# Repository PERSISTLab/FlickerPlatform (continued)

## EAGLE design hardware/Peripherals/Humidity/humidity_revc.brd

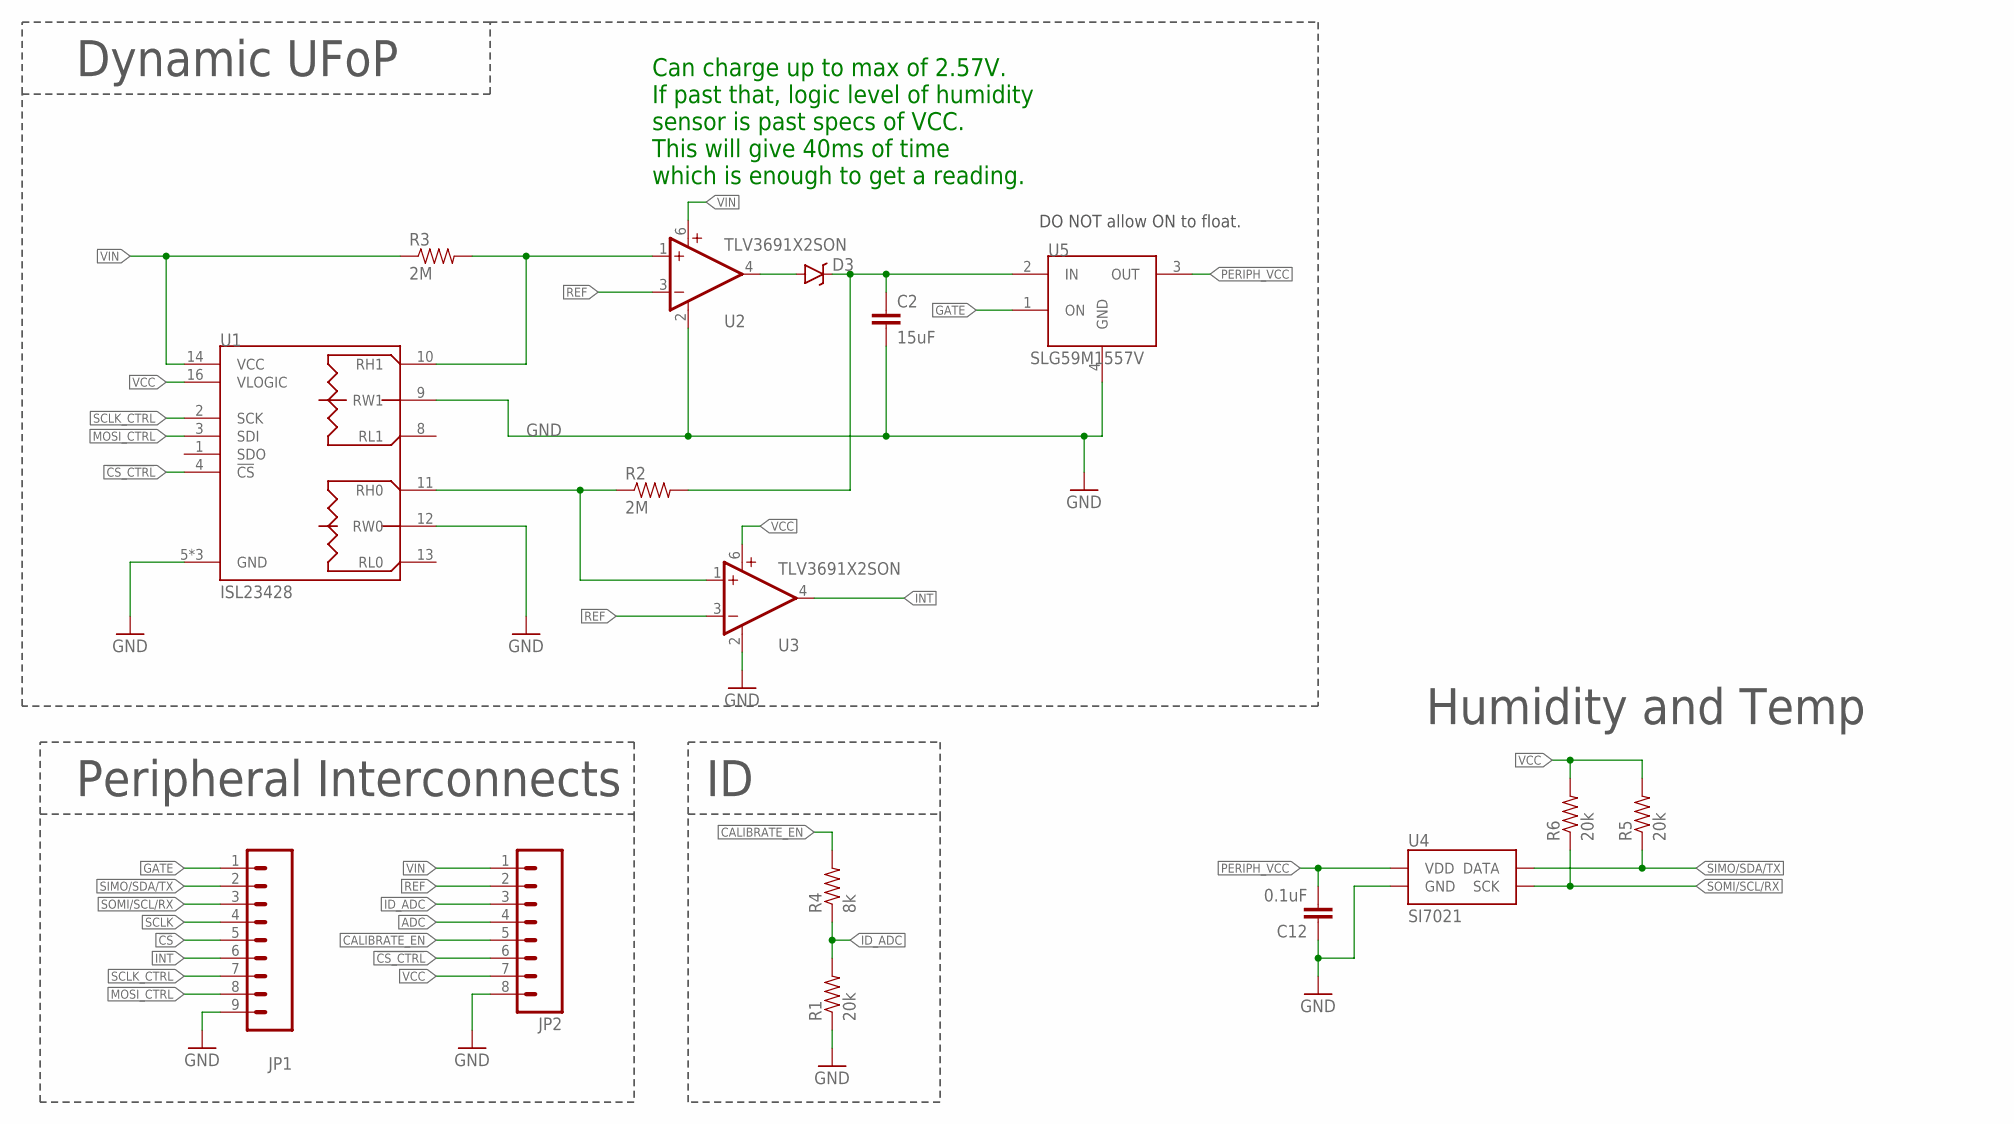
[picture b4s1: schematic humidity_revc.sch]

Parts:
C2: 15uF; 0805; MPN C2012X7S1A156M125AC; DIGIKEY 445-14559-1-ND
C12: 0.1uF; 0402; MPN 0402YD104KAT2A
D3: RB751; SOD-523; MPN BAS40-02V-V-G-08; DIGIKEY BAS40-02V-V-G-08GICT-ND
JP1: M091.27MM; 1X09-1.27MM; MANUFACTURERPARTNUMBER GRPB091VWVN-RC; DIGIKEY S9014E-09-ND
JP2: M081.27MM; 1X08-1.27MM; MANUFACTURERPARTNUMBER GRPB081VWVN-RC; DIGIKEY S9014E-08-ND
R1, R5, R6: 20k; 0402; MPN ERJ-2RKF2002X
R2, R3: 2M; 0402; MPN RC1005F205CS; DIGIKEY 1276-4293-1-ND
R4: 8k; 0402; MPN RC0402JR-078K2L
U1: ISL23428; UTQFN-16; MPN ISL23428TFRUZ-T7A; DIGIKEY ISL23428TFRUZ-T7ACT-ND
U2, U3: TLV3691X2SON; X2SON; MPN TLV3691IDPFR; DIGIKEY 296-37242-1-ND
U4: SI7021; MPN SI7021-A20-GM; DIGIKEY 336-3140-5-ND
U5: SLG59M1557V; 4STDFN; MPN SLG59M1557V; MOUSER 402-SLG59M1557V

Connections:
!CS: JP1.5
!CS_CTRL: JP2.6, U1.4 (!CS)
ADC: JP2.4
CALIBRATE_EN: JP2.5, R4.2
GATE: JP1.1, U5.1 (ON)
GND: C2.2, C12.1, JP1.9, JP2.8, R1.1, U1.5 (GND), U1.6 (GND), U1.9 (RW1), U1.12 (RW0), U1.15 (GND), U2.2 (GND), U3.2 (GND), U4.GND, U5.4 (GND)
ID_ADC: JP2.3, R1.2, R4.1
INT: JP1.6, U3.4 (OUT)
MOSI_CTRL: JP1.8, U1.3 (SDI)
unnamed: D3.A, U2.4 (OUT)
unnamed: C2.1, D3.C, R2.2, U5.2 (IN)
unnamed: R3.2, U1.10 (RH1), U2.1 (+IN)
unnamed: R2.1, U1.11 (RH0), U3.1 (+IN)
PERIPH_VCC: C12.2, U4.VDD, U5.3 (OUT)
REF: JP2.2, U2.3 (-IN), U3.3 (-IN)
SCLK: JP1.4
SCLK_CTRL: JP1.7, U1.2 (SCK)
SIMO/SDA/TX: JP1.2, R5.1, U4.DATA
SOMI/SCL/RX: JP1.3, R6.1, U4.SCK
VCC: JP2.7, R5.2, R6.2, U1.16 (VLOGIC), U3.6 (V+)
VIN: JP2.1, R3.1, U1.14 (VCC), U2.6 (V+)

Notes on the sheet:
DO NOT allow ON to float.
Peripheral Interconnects
Dynamic UFoP
Humidity and Temp
Can charge up to max of 2.57V. If past that, logic level of humidity sensor is past specs of VCC. This will give 40ms of time which is enough to get a reading.

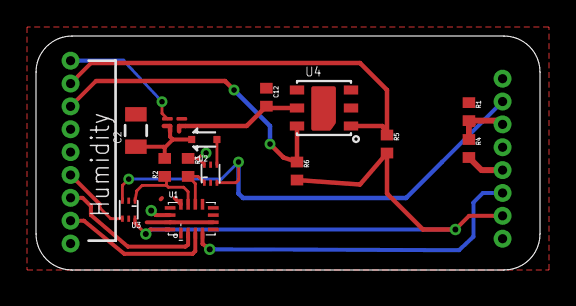
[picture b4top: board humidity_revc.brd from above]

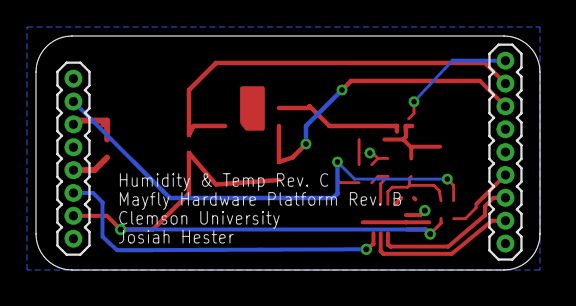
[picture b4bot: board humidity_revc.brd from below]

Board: 2 copper layers, 28.0 x 13.0 mm, 16 parts (2 on the bottom side), 18 nets.

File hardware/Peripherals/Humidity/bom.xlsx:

Part | Value | Device | Package | Description | DIGIKEY | MANUFACTURERPARTNUMBER | MOUSER | MPN | PROD_ID | VALUE
C2 | 15uF | CAP0805 | 805 | Capacitor | 445-14559-1-ND |  |  | C2012X7S1A156M125AC
C12 | 0.1uF | C-EU | 402 |  |  |  |  | 0402YD104KAT2A
D3 | RB751 | DIODE-SCHOTTKY-RB751 | SOD-523 | Schottky diodes in SFE's production catalog | BAS40-02V-V-G-08GICT-ND |  |  | BAS40-02V-V-G-08 | DIO-11018 | RB751
JP1 |  | M091.27MM | 1X09-1.27MM | Header 9 | S9014E-09-ND | GRPB091VWVN-RC |  | GRPB091VWVN-RC
JP2 |  | M081.27MM | 1X08-1.27MM | Header 8 | S9014E-08-ND | GRPB081VWVN-RC |  | GRPB081VWVN-RC
R1 | 20k | R-EU | 402 |  |  |  |  | ERJ-2RKF2002X
R2 | 2M | R-EU | 402 |  | 1276-4293-1-ND |  |  | RC1005F205CS
R3 | 2M | R-EU | 402 |  | 1276-4293-1-ND |  |  | RC1005F205CS
R4 | 8k | R-EU | 402 |  |  |  |  | RC0402JR-078K2L
R5 | 20k | R-EU | 402 |  |  |  |  | ERJ-2RKF2002X
R6 | 20k | R-EU | 402 |  |  |  |  | ERJ-2RKF2002X
U1 | ISL23428 | ISL23428 | UTQFN-16 | Intersil: Dual, 128-Tap, Low Voltage Digitally Controlled | ISL23428TFRUZ-T7ACT-ND |  |  | ISL23428TFRUZ-T7A
U2 | TLV3691X2SON | TLV3691X2SON | X2SON | 0.9-V to 6.5-V, Nanopower Comparator | 296-37242-1-ND |  |  | TLV3691IDPFR
U3 | TLV3691X2SON | TLV3691X2SON | X2SON | 0.9-V to 6.5-V, Nanopower Comparator | 296-37242-1-ND |  |  | TLV3691IDPFR
U4 | SI7021 | SI7021 | SI7021 | The Si7021 is an I2C Humidity and Temperature Sensor | 336-3140-5-ND |  |  | SI7021-A20-GM
U5 | SLG59M1557V | SLG59M1557V | 4STDFN | SILEGO SLG59M1557V: Ultra-small 28.5 mŒ©, 1.0 A |  |  | 402-SLG59M1557V | SLG59M1557V
